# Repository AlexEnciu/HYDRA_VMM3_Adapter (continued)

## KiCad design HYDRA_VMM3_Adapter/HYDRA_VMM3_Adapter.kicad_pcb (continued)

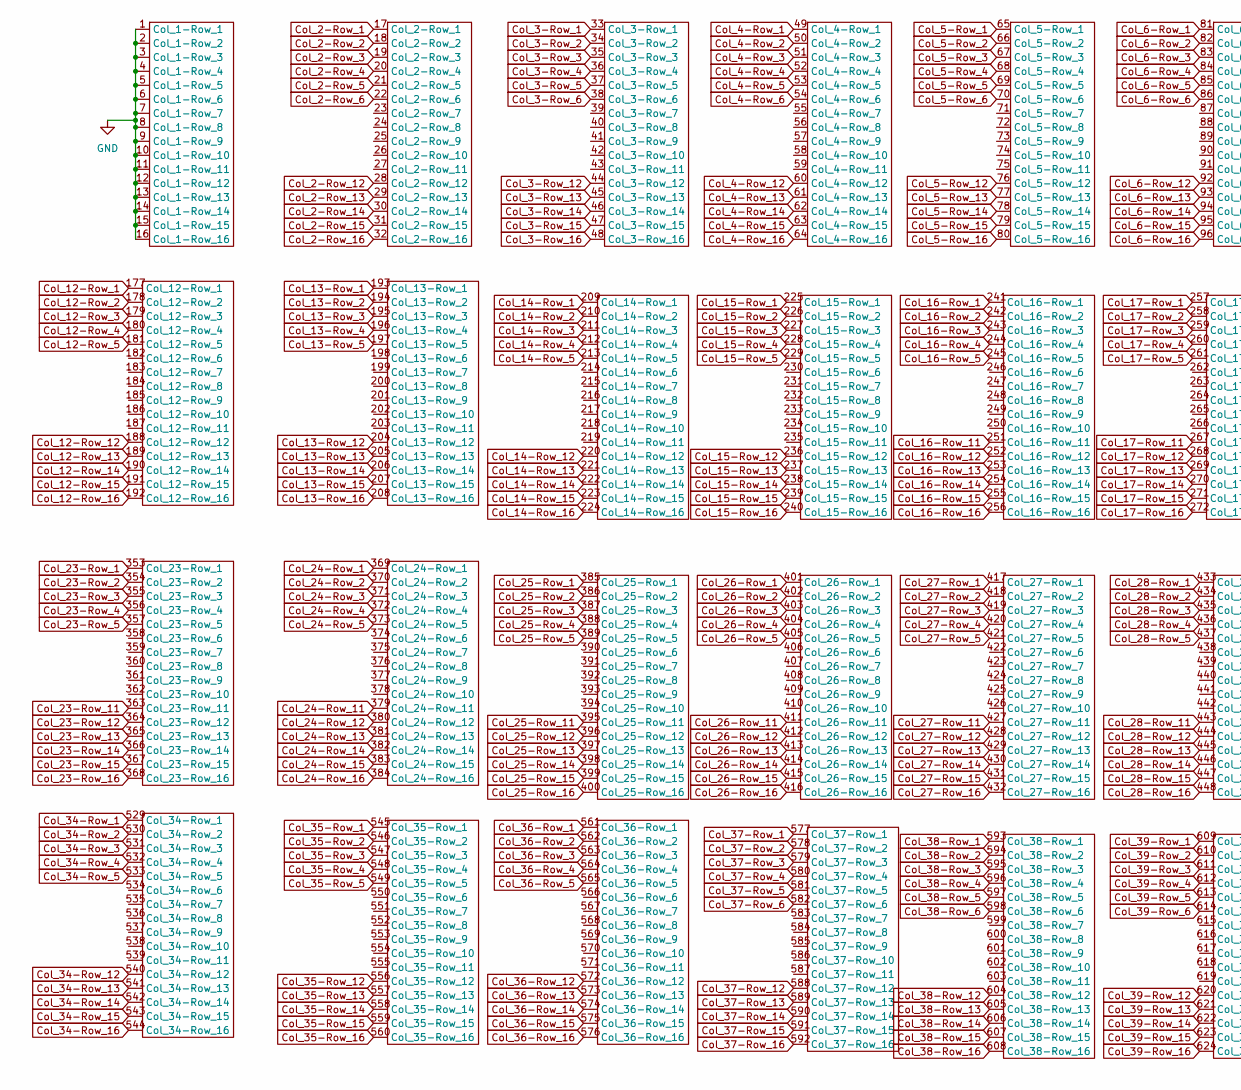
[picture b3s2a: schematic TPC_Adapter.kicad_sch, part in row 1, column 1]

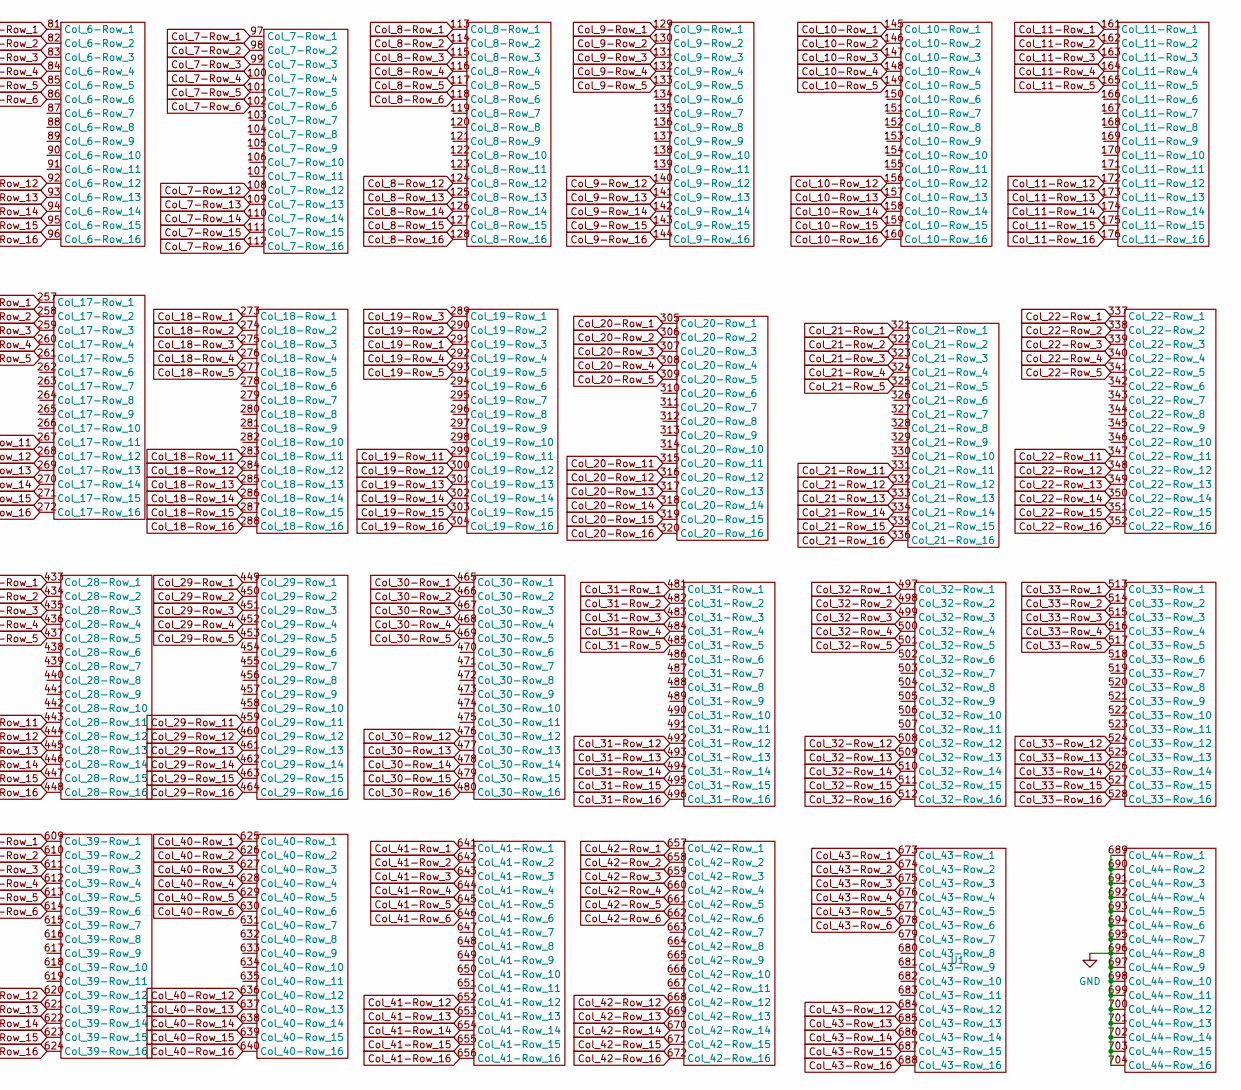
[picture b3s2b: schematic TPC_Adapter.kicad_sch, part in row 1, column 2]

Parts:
U1: TPC_Adapter_Footprint

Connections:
Col_2-Row_1: U1.17 (Col_2-Row_1); also elsewhere on the board
Col_2-Row_2: U1.18 (Col_2-Row_2); also elsewhere on the board
Col_2-Row_3: U1.19 (Col_2-Row_3); also elsewhere on the board
Col_2-Row_4: U1.20 (Col_2-Row_4); also elsewhere on the board
Col_2-Row_5: U1.21 (Col_2-Row_5); also elsewhere on the board
Col_2-Row_6: U1.22 (Col_2-Row_6); also elsewhere on the board
Col_2-Row_12: U1.28 (Col_2-Row_12); also elsewhere on the board
Col_2-Row_13: U1.29 (Col_2-Row_13); also elsewhere on the board
Col_2-Row_14: U1.30 (Col_2-Row_14); also elsewhere on the board
Col_2-Row_15: U1.31 (Col_2-Row_15); also elsewhere on the board
Col_2-Row_16: U1.32 (Col_2-Row_16); also elsewhere on the board
Col_3-Row_1: U1.33 (Col_3-Row_1); also elsewhere on the board
Col_3-Row_2: U1.34 (Col_3-Row_2); also elsewhere on the board
Col_3-Row_3: U1.35 (Col_3-Row_3); also elsewhere on the board
Col_3-Row_4: U1.36 (Col_3-Row_4); also elsewhere on the board
Col_3-Row_5: U1.37 (Col_3-Row_5); also elsewhere on the board
Col_3-Row_6: U1.38 (Col_3-Row_6); also elsewhere on the board
Col_3-Row_12: U1.44 (Col_3-Row_12); also elsewhere on the board
Col_3-Row_13: U1.45 (Col_3-Row_13); also elsewhere on the board
Col_3-Row_14: U1.46 (Col_3-Row_14); also elsewhere on the board
Col_3-Row_15: U1.47 (Col_3-Row_15); also elsewhere on the board
Col_3-Row_16: U1.48 (Col_3-Row_16); also elsewhere on the board
Col_4-Row_1: U1.49 (Col_4-Row_1); also elsewhere on the board
Col_4-Row_2: U1.50 (Col_4-Row_2); also elsewhere on the board
Col_4-Row_3: U1.51 (Col_4-Row_3); also elsewhere on the board
Col_4-Row_4: U1.52 (Col_4-Row_4); also elsewhere on the board
Col_4-Row_5: U1.53 (Col_4-Row_5); also elsewhere on the board
Col_4-Row_6: U1.54 (Col_4-Row_6); also elsewhere on the board
Col_4-Row_12: U1.60 (Col_4-Row_12); also elsewhere on the board
Col_4-Row_13: U1.61 (Col_4-Row_13); also elsewhere on the board
Col_4-Row_14: U1.62 (Col_4-Row_14); also elsewhere on the board
Col_4-Row_15: U1.63 (Col_4-Row_15); also elsewhere on the board
Col_4-Row_16: U1.64 (Col_4-Row_16); also elsewhere on the board
Col_5-Row_1: U1.65 (Col_5-Row_1); also elsewhere on the board
Col_5-Row_2: U1.66 (Col_5-Row_2); also elsewhere on the board
Col_5-Row_3: U1.67 (Col_5-Row_3); also elsewhere on the board
Col_5-Row_4: U1.68 (Col_5-Row_4); also elsewhere on the board
Col_5-Row_5: U1.69 (Col_5-Row_5); also elsewhere on the board
Col_5-Row_6: U1.70 (Col_5-Row_6); also elsewhere on the board
Col_5-Row_12: U1.76 (Col_5-Row_12); also elsewhere on the board
Col_5-Row_13: U1.77 (Col_5-Row_13); also elsewhere on the board
Col_5-Row_14: U1.78 (Col_5-Row_14); also elsewhere on the board
Col_5-Row_15: U1.79 (Col_5-Row_15); also elsewhere on the board
Col_5-Row_16: U1.80 (Col_5-Row_16); also elsewhere on the board
Col_6-Row_1: U1.81 (Col_6-Row_1); also elsewhere on the board
Col_6-Row_2: U1.82 (Col_6-Row_2); also elsewhere on the board
Col_6-Row_3: U1.83 (Col_6-Row_3); also elsewhere on the board
Col_6-Row_4: U1.84 (Col_6-Row_4); also elsewhere on the board
Col_6-Row_5: U1.85 (Col_6-Row_5); also elsewhere on the board
Col_6-Row_6: U1.86 (Col_6-Row_6); also elsewhere on the board
Col_6-Row_12: U1.92 (Col_6-Row_12); also elsewhere on the board
Col_6-Row_13: U1.93 (Col_6-Row_13); also elsewhere on the board
Col_6-Row_14: U1.94 (Col_6-Row_14); also elsewhere on the board
Col_6-Row_15: U1.95 (Col_6-Row_15); also elsewhere on the board
Col_6-Row_16: U1.96 (Col_6-Row_16); also elsewhere on the board
Col_7-Row_1: U1.97 (Col_7-Row_1); also elsewhere on the board
Col_7-Row_2: U1.98 (Col_7-Row_2); also elsewhere on the board
Col_7-Row_3: U1.99 (Col_7-Row_3); also elsewhere on the board
Col_7-Row_4: U1.100 (Col_7-Row_4); also elsewhere on the board
Col_7-Row_5: U1.101 (Col_7-Row_5); also elsewhere on the board
Col_7-Row_6: U1.102 (Col_7-Row_6); also elsewhere on the board
Col_7-Row_12: U1.108 (Col_7-Row_12); also elsewhere on the board
Col_7-Row_13: U1.109 (Col_7-Row_13); also elsewhere on the board
Col_7-Row_14: U1.110 (Col_7-Row_14); also elsewhere on the board
Col_7-Row_15: U1.111 (Col_7-Row_15); also elsewhere on the board
Col_7-Row_16: U1.112 (Col_7-Row_16); also elsewhere on the board
Col_8-Row_1: U1.113 (Col_8-Row_1); also elsewhere on the board
Col_8-Row_2: U1.114 (Col_8-Row_2); also elsewhere on the board
Col_8-Row_3: U1.115 (Col_8-Row_3); also elsewhere on the board
Col_8-Row_4: U1.116 (Col_8-Row_4); also elsewhere on the board
Col_8-Row_5: U1.117 (Col_8-Row_5); also elsewhere on the board
Col_8-Row_6: U1.118 (Col_8-Row_6); also elsewhere on the board
Col_8-Row_12: U1.124 (Col_8-Row_12); also elsewhere on the board
Col_8-Row_13: U1.125 (Col_8-Row_13); also elsewhere on the board
Col_8-Row_14: U1.126 (Col_8-Row_14); also elsewhere on the board
Col_8-Row_15: U1.127 (Col_8-Row_15); also elsewhere on the board
Col_8-Row_16: U1.128 (Col_8-Row_16); also elsewhere on the board
Col_9-Row_1: U1.129 (Col_9-Row_1); also elsewhere on the board
Col_9-Row_2: U1.130 (Col_9-Row_2); also elsewhere on the board
Col_9-Row_3: U1.131 (Col_9-Row_3); also elsewhere on the board
Col_9-Row_4: U1.132 (Col_9-Row_4); also elsewhere on the board
Col_9-Row_5: U1.133 (Col_9-Row_5); also elsewhere on the board
Col_9-Row_12: U1.140 (Col_9-Row_12); also elsewhere on the board
Col_9-Row_13: U1.141 (Col_9-Row_13); also elsewhere on the board
Col_9-Row_14: U1.142 (Col_9-Row_14); also elsewhere on the board
Col_9-Row_15: U1.143 (Col_9-Row_15); also elsewhere on the board
Col_9-Row_16: U1.144 (Col_9-Row_16); also elsewhere on the board
Col_10-Row_1: U1.145 (Col_10-Row_1); also elsewhere on the board
Col_10-Row_2: U1.146 (Col_10-Row_2); also elsewhere on the board
Col_10-Row_3: U1.147 (Col_10-Row_3); also elsewhere on the board
Col_10-Row_4: U1.148 (Col_10-Row_4); also elsewhere on the board
Col_10-Row_5: U1.149 (Col_10-Row_5); also elsewhere on the board
Col_10-Row_12: U1.156 (Col_10-Row_12); also elsewhere on the board
Col_10-Row_13: U1.157 (Col_10-Row_13); also elsewhere on the board
Col_10-Row_14: U1.158 (Col_10-Row_14); also elsewhere on the board
Col_10-Row_15: U1.159 (Col_10-Row_15); also elsewhere on the board
Col_10-Row_16: U1.160 (Col_10-Row_16); also elsewhere on the board
Col_11-Row_1: U1.161 (Col_11-Row_1); also elsewhere on the board
Col_11-Row_2: U1.162 (Col_11-Row_2); also elsewhere on the board
Col_11-Row_3: U1.163 (Col_11-Row_3); also elsewhere on the board
Col_11-Row_4: U1.164 (Col_11-Row_4); also elsewhere on the board
Col_11-Row_5: U1.165 (Col_11-Row_5); also elsewhere on the board
Col_11-Row_12: U1.172 (Col_11-Row_12); also elsewhere on the board
Col_11-Row_13: U1.173 (Col_11-Row_13); also elsewhere on the board
Col_11-Row_14: U1.174 (Col_11-Row_14); also elsewhere on the board
Col_11-Row_15: U1.175 (Col_11-Row_15); also elsewhere on the board
Col_11-Row_16: U1.176 (Col_11-Row_16); also elsewhere on the board
Col_12-Row_1: U1.177 (Col_12-Row_1); also elsewhere on the board
Col_12-Row_2: U1.178 (Col_12-Row_2); also elsewhere on the board
Col_12-Row_3: U1.179 (Col_12-Row_3); also elsewhere on the board
Col_12-Row_4: U1.180 (Col_12-Row_4); also elsewhere on the board
Col_12-Row_5: U1.181 (Col_12-Row_5); also elsewhere on the board
Col_12-Row_12: U1.188 (Col_12-Row_12); also elsewhere on the board
Col_12-Row_13: U1.189 (Col_12-Row_13); also elsewhere on the board
Col_12-Row_14: U1.190 (Col_12-Row_14); also elsewhere on the board
Col_12-Row_15: U1.191 (Col_12-Row_15); also elsewhere on the board
Col_12-Row_16: U1.192 (Col_12-Row_16); also elsewhere on the board
Col_13-Row_1: U1.193 (Col_13-Row_1); also elsewhere on the board
Col_13-Row_2: U1.194 (Col_13-Row_2); also elsewhere on the board
Col_13-Row_3: U1.195 (Col_13-Row_3); also elsewhere on the board
Col_13-Row_4: U1.196 (Col_13-Row_4); also elsewhere on the board
Col_13-Row_5: U1.197 (Col_13-Row_5); also elsewhere on the board
Col_13-Row_12: U1.204 (Col_13-Row_12); also elsewhere on the board
Col_13-Row_13: U1.205 (Col_13-Row_13); also elsewhere on the board
Col_13-Row_14: U1.206 (Col_13-Row_14); also elsewhere on the board
Col_13-Row_15: U1.207 (Col_13-Row_15); also elsewhere on the board
Col_13-Row_16: U1.208 (Col_13-Row_16); also elsewhere on the board
Col_14-Row_1: U1.209 (Col_14-Row_1); also elsewhere on the board
Col_14-Row_2: U1.210 (Col_14-Row_2); also elsewhere on the board
Col_14-Row_3: U1.211 (Col_14-Row_3); also elsewhere on the board
Col_14-Row_4: U1.212 (Col_14-Row_4); also elsewhere on the board
Col_14-Row_5: U1.213 (Col_14-Row_5); also elsewhere on the board
Col_14-Row_12: U1.220 (Col_14-Row_12); also elsewhere on the board
Col_14-Row_13: U1.221 (Col_14-Row_13); also elsewhere on the board
Col_14-Row_14: U1.222 (Col_14-Row_14); also elsewhere on the board
Col_14-Row_15: U1.223 (Col_14-Row_15); also elsewhere on the board
Col_14-Row_16: U1.224 (Col_14-Row_16); also elsewhere on the board
Col_15-Row_1: U1.225 (Col_15-Row_1); also elsewhere on the board
Col_15-Row_2: U1.226 (Col_15-Row_2); also elsewhere on the board
Col_15-Row_3: U1.227 (Col_15-Row_3); also elsewhere on the board
Col_15-Row_4: U1.228 (Col_15-Row_4); also elsewhere on the board
Col_15-Row_5: U1.229 (Col_15-Row_5); also elsewhere on the board
Col_15-Row_12: U1.236 (Col_15-Row_12); also elsewhere on the board
Col_15-Row_13: U1.237 (Col_15-Row_13); also elsewhere on the board
Col_15-Row_14: U1.238 (Col_15-Row_14); also elsewhere on the board
Col_15-Row_15: U1.239 (Col_15-Row_15); also elsewhere on the board
Col_15-Row_16: U1.240 (Col_15-Row_16); also elsewhere on the board
Col_16-Row_1: U1.241 (Col_16-Row_1); also elsewhere on the board
Col_16-Row_2: U1.242 (Col_16-Row_2); also elsewhere on the board
Col_16-Row_3: U1.243 (Col_16-Row_3); also elsewhere on the board
Col_16-Row_4: U1.244 (Col_16-Row_4); also elsewhere on the board
Col_16-Row_5: U1.245 (Col_16-Row_5); also elsewhere on the board
Col_16-Row_11: U1.251 (Col_16-Row_11); also elsewhere on the board
Col_16-Row_12: U1.252 (Col_16-Row_12); also elsewhere on the board
Col_16-Row_13: U1.253 (Col_16-Row_13); also elsewhere on the board
Col_16-Row_14: U1.254 (Col_16-Row_14); also elsewhere on the board
Col_16-Row_15: U1.255 (Col_16-Row_15); also elsewhere on the board
Col_16-Row_16: U1.256 (Col_16-Row_16); also elsewhere on the board
Col_17-Row_1: U1.257 (Col_17-Row_1); also elsewhere on the board
Col_17-Row_2: U1.258 (Col_17-Row_2); also elsewhere on the board
Col_17-Row_3: U1.259 (Col_17-Row_3); also elsewhere on the board
Col_17-Row_4: U1.260 (Col_17-Row_4); also elsewhere on the board
Col_17-Row_5: U1.261 (Col_17-Row_5); also elsewhere on the board
Col_17-Row_11: U1.267 (Col_17-Row_11); also elsewhere on the board
Col_17-Row_12: U1.268 (Col_17-Row_12); also elsewhere on the board
Col_17-Row_13: U1.269 (Col_17-Row_13); also elsewhere on the board
Col_17-Row_14: U1.270 (Col_17-Row_14); also elsewhere on the board
Col_17-Row_15: U1.271 (Col_17-Row_15); also elsewhere on the board
Col_17-Row_16: U1.272 (Col_17-Row_16); also elsewhere on the board
Col_18-Row_1: U1.273 (Col_18-Row_1); also elsewhere on the board
Col_18-Row_2: U1.274 (Col_18-Row_2); also elsewhere on the board
Col_18-Row_3: U1.275 (Col_18-Row_3); also elsewhere on the board
Col_18-Row_4: U1.276 (Col_18-Row_4); also elsewhere on the board
Col_18-Row_5: U1.277 (Col_18-Row_5); also elsewhere on the board
Col_18-Row_11: U1.283 (Col_18-Row_11); also elsewhere on the board
Col_18-Row_12: U1.284 (Col_18-Row_12); also elsewhere on the board
Col_18-Row_13: U1.285 (Col_18-Row_13); also elsewhere on the board
Col_18-Row_14: U1.286 (Col_18-Row_14); also elsewhere on the board
Col_18-Row_15: U1.287 (Col_18-Row_15); also elsewhere on the board
Col_18-Row_16: U1.288 (Col_18-Row_16); also elsewhere on the board
Col_19-Row_1: U1.291 (Col_19-Row_3); also elsewhere on the board
Col_19-Row_2: U1.290 (Col_19-Row_2); also elsewhere on the board
Col_19-Row_3: U1.289 (Col_19-Row_1); also elsewhere on the board
Col_19-Row_4: U1.292 (Col_19-Row_4); also elsewhere on the board
Col_19-Row_5: U1.293 (Col_19-Row_5); also elsewhere on the board
Col_19-Row_11: U1.299 (Col_19-Row_11); also elsewhere on the board
Col_19-Row_12: U1.300 (Col_19-Row_12); also elsewhere on the board
Col_19-Row_13: U1.301 (Col_19-Row_13); also elsewhere on the board
Col_19-Row_14: U1.302 (Col_19-Row_14); also elsewhere on the board
Col_19-Row_15: U1.303 (Col_19-Row_15); also elsewhere on the board
Col_19-Row_16: U1.304 (Col_19-Row_16); also elsewhere on the board
Col_20-Row_1: U1.305 (Col_20-Row_1); also elsewhere on the board
Col_20-Row_2: U1.306 (Col_20-Row_2); also elsewhere on the board
Col_20-Row_3: U1.307 (Col_20-Row_3); also elsewhere on the board
Col_20-Row_4: U1.308 (Col_20-Row_4); also elsewhere on the board
Col_20-Row_5: U1.309 (Col_20-Row_5); also elsewhere on the board
Col_20-Row_11: U1.315 (Col_20-Row_11); also elsewhere on the board
Col_20-Row_12: U1.316 (Col_20-Row_12); also elsewhere on the board
Col_20-Row_13: U1.317 (Col_20-Row_13); also elsewhere on the board
Col_20-Row_14: U1.318 (Col_20-Row_14); also elsewhere on the board
Col_20-Row_15: U1.319 (Col_20-Row_15); also elsewhere on the board
Col_20-Row_16: U1.320 (Col_20-Row_16); also elsewhere on the board
Col_21-Row_1: U1.321 (Col_21-Row_1); also elsewhere on the board
Col_21-Row_2: U1.322 (Col_21-Row_2); also elsewhere on the board
Col_21-Row_3: U1.323 (Col_21-Row_3); also elsewhere on the board
Col_21-Row_4: U1.324 (Col_21-Row_4); also elsewhere on the board
Col_21-Row_5: U1.325 (Col_21-Row_5); also elsewhere on the board
Col_21-Row_11: U1.331 (Col_21-Row_11); also elsewhere on the board
Col_21-Row_12: U1.332 (Col_21-Row_12); also elsewhere on the board
Col_21-Row_13: U1.333 (Col_21-Row_13); also elsewhere on the board
Col_21-Row_14: U1.334 (Col_21-Row_14); also elsewhere on the board
Col_21-Row_15: U1.335 (Col_21-Row_15); also elsewhere on the board
Col_21-Row_16: U1.336 (Col_21-Row_16); also elsewhere on the board
Col_22-Row_1: U1.337 (Col_22-Row_1); also elsewhere on the board
Col_22-Row_2: U1.338 (Col_22-Row_2); also elsewhere on the board
Col_22-Row_3: U1.339 (Col_22-Row_3); also elsewhere on the board
Col_22-Row_4: U1.340 (Col_22-Row_4); also elsewhere on the board
Col_22-Row_5: U1.341 (Col_22-Row_5); also elsewhere on the board
Col_22-Row_11: U1.347 (Col_22-Row_11); also elsewhere on the board
Col_22-Row_12: U1.348 (Col_22-Row_12); also elsewhere on the board
Col_22-Row_13: U1.349 (Col_22-Row_13); also elsewhere on the board
Col_22-Row_14: U1.350 (Col_22-Row_14); also elsewhere on the board
Col_22-Row_15: U1.351 (Col_22-Row_15); also elsewhere on the board
Col_22-Row_16: U1.352 (Col_22-Row_16); also elsewhere on the board
Col_23-Row_1: U1.353 (Col_23-Row_1); also elsewhere on the board
Col_23-Row_2: U1.354 (Col_23-Row_2); also elsewhere on the board
Col_23-Row_3: U1.355 (Col_23-Row_3); also elsewhere on the board
Col_23-Row_4: U1.356 (Col_23-Row_4); also elsewhere on the board
Col_23-Row_5: U1.357 (Col_23-Row_5); also elsewhere on the board
Col_23-Row_11: U1.363 (Col_23-Row_11); also elsewhere on the board
Col_23-Row_12: U1.364 (Col_23-Row_12); also elsewhere on the board
Col_23-Row_13: U1.365 (Col_23-Row_13); also elsewhere on the board
Col_23-Row_14: U1.366 (Col_23-Row_14); also elsewhere on the board
Col_23-Row_15: U1.367 (Col_23-Row_15); also elsewhere on the board
Col_23-Row_16: U1.368 (Col_23-Row_16); also elsewhere on the board
Col_24-Row_1: U1.369 (Col_24-Row_1); also elsewhere on the board
Col_24-Row_2: U1.370 (Col_24-Row_2); also elsewhere on the board
Col_24-Row_3: U1.371 (Col_24-Row_3); also elsewhere on the board
Col_24-Row_4: U1.372 (Col_24-Row_4); also elsewhere on the board
Col_24-Row_5: U1.373 (Col_24-Row_5); also elsewhere on the board
Col_24-Row_11: U1.379 (Col_24-Row_11); also elsewhere on the board
Col_24-Row_12: U1.380 (Col_24-Row_12); also elsewhere on the board
Col_24-Row_13: U1.381 (Col_24-Row_13); also elsewhere on the board
Col_24-Row_14: U1.382 (Col_24-Row_14); also elsewhere on the board
Col_24-Row_15: U1.383 (Col_24-Row_15); also elsewhere on the board
Col_24-Row_16: U1.384 (Col_24-Row_16); also elsewhere on the board
Col_25-Row_1: U1.385 (Col_25-Row_1); also elsewhere on the board
Col_25-Row_2: U1.386 (Col_25-Row_2); also elsewhere on the board
Col_25-Row_3: U1.387 (Col_25-Row_3); also elsewhere on the board
Col_25-Row_4: U1.388 (Col_25-Row_4); also elsewhere on the board
Col_25-Row_5: U1.389 (Col_25-Row_5); also elsewhere on the board
Col_25-Row_11: U1.395 (Col_25-Row_11); also elsewhere on the board
Col_25-Row_12: U1.396 (Col_25-Row_12); also elsewhere on the board
Col_25-Row_13: U1.397 (Col_25-Row_13); also elsewhere on the board
Col_25-Row_14: U1.398 (Col_25-Row_14); also elsewhere on the board
Col_25-Row_15: U1.399 (Col_25-Row_15); also elsewhere on the board
Col_25-Row_16: U1.400 (Col_25-Row_16); also elsewhere on the board
Col_26-Row_1: U1.401 (Col_26-Row_1); also elsewhere on the board
Col_26-Row_2: U1.402 (Col_26-Row_2); also elsewhere on the board
Col_26-Row_3: U1.403 (Col_26-Row_3); also elsewhere on the board
Col_26-Row_4: U1.404 (Col_26-Row_4); also elsewhere on the board
Col_26-Row_5: U1.405 (Col_26-Row_5); also elsewhere on the board
Col_26-Row_11: U1.411 (Col_26-Row_11); also elsewhere on the board
Col_26-Row_12: U1.412 (Col_26-Row_12); also elsewhere on the board
Col_26-Row_13: U1.413 (Col_26-Row_13); also elsewhere on the board
Col_26-Row_14: U1.414 (Col_26-Row_14); also elsewhere on the board
Col_26-Row_15: U1.415 (Col_26-Row_15); also elsewhere on the board
Col_26-Row_16: U1.416 (Col_26-Row_16); also elsewhere on the board
Col_27-Row_1: U1.417 (Col_27-Row_1); also elsewhere on the board
Col_27-Row_2: U1.418 (Col_27-Row_2); also elsewhere on the board
Col_27-Row_3: U1.419 (Col_27-Row_3); also elsewhere on the board
Col_27-Row_4: U1.420 (Col_27-Row_4); also elsewhere on the board
Col_27-Row_5: U1.421 (Col_27-Row_5); also elsewhere on the board
Col_27-Row_11: U1.427 (Col_27-Row_11); also elsewhere on the board
Col_27-Row_12: U1.428 (Col_27-Row_12); also elsewhere on the board
Col_27-Row_13: U1.429 (Col_27-Row_13); also elsewhere on the board
Col_27-Row_14: U1.430 (Col_27-Row_14); also elsewhere on the board
Col_27-Row_15: U1.431 (Col_27-Row_15); also elsewhere on the board
Col_27-Row_16: U1.432 (Col_27-Row_16); also elsewhere on the board
Col_28-Row_1: U1.433 (Col_28-Row_1); also elsewhere on the board
Col_28-Row_2: U1.434 (Col_28-Row_2); also elsewhere on the board
Col_28-Row_3: U1.435 (Col_28-Row_3); also elsewhere on the board
Col_28-Row_4: U1.436 (Col_28-Row_4); also elsewhere on the board
Col_28-Row_5: U1.437 (Col_28-Row_5); also elsewhere on the board
Col_28-Row_11: U1.443 (Col_28-Row_11); also elsewhere on the board
Col_28-Row_12: U1.444 (Col_28-Row_12); also elsewhere on the board
Col_28-Row_13: U1.445 (Col_28-Row_13); also elsewhere on the board
Col_28-Row_14: U1.446 (Col_28-Row_14); also elsewhere on the board
Col_28-Row_15: U1.447 (Col_28-Row_15); also elsewhere on the board
Col_28-Row_16: U1.448 (Col_28-Row_16); also elsewhere on the board
Col_29-Row_1: U1.449 (Col_29-Row_1); also elsewhere on the board
Col_29-Row_2: U1.450 (Col_29-Row_2); also elsewhere on the board
Col_29-Row_3: U1.451 (Col_29-Row_3); also elsewhere on the board
Col_29-Row_4: U1.452 (Col_29-Row_4); also elsewhere on the board
Col_29-Row_5: U1.453 (Col_29-Row_5); also elsewhere on the board
Col_29-Row_11: U1.459 (Col_29-Row_11); also elsewhere on the board
Col_29-Row_12: U1.460 (Col_29-Row_12); also elsewhere on the board
Col_29-Row_13: U1.461 (Col_29-Row_13); also elsewhere on the board
Col_29-Row_14: U1.462 (Col_29-Row_14); also elsewhere on the board
Col_29-Row_15: U1.463 (Col_29-Row_15); also elsewhere on the board
Col_29-Row_16: U1.464 (Col_29-Row_16); also elsewhere on the board
Col_30-Row_1: U1.465 (Col_30-Row_1); also elsewhere on the board
Col_30-Row_2: U1.466 (Col_30-Row_2); also elsewhere on the board
Col_30-Row_3: U1.467 (Col_30-Row_3); also elsewhere on the board
Col_30-Row_4: U1.468 (Col_30-Row_4); also elsewhere on the board
Col_30-Row_5: U1.469 (Col_30-Row_5); also elsewhere on the board
Col_30-Row_12: U1.476 (Col_30-Row_12); also elsewhere on the board
Col_30-Row_13: U1.477 (Col_30-Row_13); also elsewhere on the board
Col_30-Row_14: U1.478 (Col_30-Row_14); also elsewhere on the board
Col_30-Row_15: U1.479 (Col_30-Row_15); also elsewhere on the board
Col_30-Row_16: U1.480 (Col_30-Row_16); also elsewhere on the board
Col_31-Row_1: U1.481 (Col_31-Row_1); also elsewhere on the board
Col_31-Row_2: U1.482 (Col_31-Row_2); also elsewhere on the board
Col_31-Row_3: U1.483 (Col_31-Row_3); also elsewhere on the board
Col_31-Row_4: U1.484 (Col_31-Row_4); also elsewhere on the board
Col_31-Row_5: U1.485 (Col_31-Row_5); also elsewhere on the board
Col_31-Row_12: U1.492 (Col_31-Row_12); also elsewhere on the board
Col_31-Row_13: U1.493 (Col_31-Row_13); also elsewhere on the board
Col_31-Row_14: U1.494 (Col_31-Row_14); also elsewhere on the board
Col_31-Row_15: U1.495 (Col_31-Row_15); also elsewhere on the board
Col_31-Row_16: U1.496 (Col_31-Row_16); also elsewhere on the board
Col_32-Row_1: U1.497 (Col_32-Row_1); also elsewhere on the board
Col_32-Row_2: U1.498 (Col_32-Row_2); also elsewhere on the board
Col_32-Row_3: U1.499 (Col_32-Row_3); also elsewhere on the board
Col_32-Row_4: U1.500 (Col_32-Row_4); also elsewhere on the board
Col_32-Row_5: U1.501 (Col_32-Row_5); also elsewhere on the board
Col_32-Row_12: U1.508 (Col_32-Row_12); also elsewhere on the board
Col_32-Row_13: U1.509 (Col_32-Row_13); also elsewhere on the board
Col_32-Row_14: U1.510 (Col_32-Row_14); also elsewhere on the board
Col_32-Row_15: U1.511 (Col_32-Row_15); also elsewhere on the board
Col_32-Row_16: U1.512 (Col_32-Row_16); also elsewhere on the board
Col_33-Row_1: U1.513 (Col_33-Row_1); also elsewhere on the board
Col_33-Row_2: U1.514 (Col_33-Row_2); also elsewhere on the board
Col_33-Row_3: U1.515 (Col_33-Row_3); also elsewhere on the board
Col_33-Row_4: U1.516 (Col_33-Row_4); also elsewhere on the board
Col_33-Row_5: U1.517 (Col_33-Row_5); also elsewhere on the board
Col_33-Row_12: U1.524 (Col_33-Row_12); also elsewhere on the board
Col_33-Row_13: U1.525 (Col_33-Row_13); also elsewhere on the board
Col_33-Row_14: U1.526 (Col_33-Row_14); also elsewhere on the board
Col_33-Row_15: U1.527 (Col_33-Row_15); also elsewhere on the board
Col_33-Row_16: U1.528 (Col_33-Row_16); also elsewhere on the board
Col_34-Row_1: U1.529 (Col_34-Row_1); also elsewhere on the board
Col_34-Row_2: U1.530 (Col_34-Row_2); also elsewhere on the board
Col_34-Row_3: U1.531 (Col_34-Row_3); also elsewhere on the board
Col_34-Row_4: U1.532 (Col_34-Row_4); also elsewhere on the board
Col_34-Row_5: U1.533 (Col_34-Row_5); also elsewhere on the board
Col_34-Row_12: U1.540 (Col_34-Row_12); also elsewhere on the board
Col_34-Row_13: U1.541 (Col_34-Row_13); also elsewhere on the board
Col_34-Row_14: U1.542 (Col_34-Row_14); also elsewhere on the board
Col_34-Row_15: U1.543 (Col_34-Row_15); also elsewhere on the board
Col_34-Row_16: U1.544 (Col_34-Row_16); also elsewhere on the board
Col_35-Row_1: U1.545 (Col_35-Row_1); also elsewhere on the board
Col_35-Row_2: U1.546 (Col_35-Row_2); also elsewhere on the board
Col_35-Row_3: U1.547 (Col_35-Row_3); also elsewhere on the board
Col_35-Row_4: U1.548 (Col_35-Row_4); also elsewhere on the board
Col_35-Row_5: U1.549 (Col_35-Row_5); also elsewhere on the board
Col_35-Row_12: U1.556 (Col_35-Row_12); also elsewhere on the board
Col_35-Row_13: U1.557 (Col_35-Row_13); also elsewhere on the board
Col_35-Row_14: U1.558 (Col_35-Row_14); also elsewhere on the board
Col_35-Row_15: U1.559 (Col_35-Row_15); also elsewhere on the board
Col_35-Row_16: U1.560 (Col_35-Row_16); also elsewhere on the board
Col_36-Row_1: U1.561 (Col_36-Row_1); also elsewhere on the board
Col_36-Row_2: U1.562 (Col_36-Row_2); also elsewhere on the board
Col_36-Row_3: U1.563 (Col_36-Row_3); also elsewhere on the board
Col_36-Row_4: U1.564 (Col_36-Row_4); also elsewhere on the board
Col_36-Row_5: U1.565 (Col_36-Row_5); also elsewhere on the board
Col_36-Row_12: U1.572 (Col_36-Row_12); also elsewhere on the board
Col_36-Row_13: U1.573 (Col_36-Row_13); also elsewhere on the board
Col_36-Row_14: U1.574 (Col_36-Row_14); also elsewhere on the board
Col_36-Row_15: U1.575 (Col_36-Row_15); also elsewhere on the board
Col_36-Row_16: U1.576 (Col_36-Row_16); also elsewhere on the board
Col_37-Row_1: U1.577 (Col_37-Row_1); also elsewhere on the board
Col_37-Row_2: U1.578 (Col_37-Row_2); also elsewhere on the board
Col_37-Row_3: U1.579 (Col_37-Row_3); also elsewhere on the board
Col_37-Row_4: U1.580 (Col_37-Row_4); also elsewhere on the board
Col_37-Row_5: U1.581 (Col_37-Row_5); also elsewhere on the board
Col_37-Row_6: U1.582 (Col_37-Row_6); also elsewhere on the board
Col_37-Row_12: U1.588 (Col_37-Row_12); also elsewhere on the board
Col_37-Row_13: U1.589 (Col_37-Row_13); also elsewhere on the board
Col_37-Row_14: U1.590 (Col_37-Row_14); also elsewhere on the board
Col_37-Row_15: U1.591 (Col_37-Row_15); also elsewhere on the board
Col_37-Row_16: U1.592 (Col_37-Row_16); also elsewhere on the board
Col_38-Row_1: U1.593 (Col_38-Row_1); also elsewhere on the board
Col_38-Row_2: U1.594 (Col_38-Row_2); also elsewhere on the board
Col_38-Row_3: U1.595 (Col_38-Row_3); also elsewhere on the board
Col_38-Row_4: U1.596 (Col_38-Row_4); also elsewhere on the board
Col_38-Row_5: U1.597 (Col_38-Row_5); also elsewhere on the board
Col_38-Row_6: U1.598 (Col_38-Row_6); also elsewhere on the board
Col_38-Row_12: U1.604 (Col_38-Row_12); also elsewhere on the board
Col_38-Row_13: U1.605 (Col_38-Row_13); also elsewhere on the board
Col_38-Row_14: U1.606 (Col_38-Row_14); also elsewhere on the board
Col_38-Row_15: U1.607 (Col_38-Row_15); also elsewhere on the board
Col_38-Row_16: U1.608 (Col_38-Row_16); also elsewhere on the board
Col_39-Row_1: U1.609 (Col_39-Row_1); also elsewhere on the board
Col_39-Row_2: U1.610 (Col_39-Row_2); also elsewhere on the board
Col_39-Row_3: U1.611 (Col_39-Row_3); also elsewhere on the board
Col_39-Row_4: U1.612 (Col_39-Row_4); also elsewhere on the board
Col_39-Row_5: U1.613 (Col_39-Row_5); also elsewhere on the board
Col_39-Row_6: U1.614 (Col_39-Row_6); also elsewhere on the board
Col_39-Row_12: U1.620 (Col_39-Row_12); also elsewhere on the board
Col_39-Row_13: U1.621 (Col_39-Row_13); also elsewhere on the board
Col_39-Row_14: U1.622 (Col_39-Row_14); also elsewhere on the board
Col_39-Row_15: U1.623 (Col_39-Row_15); also elsewhere on the board
Col_39-Row_16: U1.624 (Col_39-Row_16); also elsewhere on the board
Col_40-Row_1: U1.625 (Col_40-Row_1); also elsewhere on the board
Col_40-Row_2: U1.626 (Col_40-Row_2); also elsewhere on the board
Col_40-Row_3: U1.627 (Col_40-Row_3); also elsewhere on the board
Col_40-Row_4: U1.628 (Col_40-Row_4); also elsewhere on the board
Col_40-Row_5: U1.629 (Col_40-Row_5); also elsewhere on the board
Col_40-Row_6: U1.630 (Col_40-Row_6); also elsewhere on the board
Col_40-Row_12: U1.636 (Col_40-Row_12); also elsewhere on the board
Col_40-Row_13: U1.637 (Col_40-Row_13); also elsewhere on the board
Col_40-Row_14: U1.638 (Col_40-Row_14); also elsewhere on the board
Col_40-Row_15: U1.639 (Col_40-Row_15); also elsewhere on the board
Col_40-Row_16: U1.640 (Col_40-Row_16); also elsewhere on the board
Col_41-Row_1: U1.641 (Col_41-Row_1); also elsewhere on the board
Col_41-Row_2: U1.642 (Col_41-Row_2); also elsewhere on the board
Col_41-Row_3: U1.643 (Col_41-Row_3); also elsewhere on the board
Col_41-Row_4: U1.644 (Col_41-Row_4); also elsewhere on the board
Col_41-Row_5: U1.645 (Col_41-Row_5); also elsewhere on the board
Col_41-Row_6: U1.646 (Col_41-Row_6); also elsewhere on the board
Col_41-Row_12: U1.652 (Col_41-Row_12); also elsewhere on the board
Col_41-Row_13: U1.653 (Col_41-Row_13); also elsewhere on the board
Col_41-Row_14: U1.654 (Col_41-Row_14); also elsewhere on the board
Col_41-Row_15: U1.655 (Col_41-Row_15); also elsewhere on the board
Col_41-Row_16: U1.656 (Col_41-Row_16); also elsewhere on the board
Col_42-Row_1: U1.657 (Col_42-Row_1); also elsewhere on the board
Col_42-Row_2: U1.658 (Col_42-Row_2); also elsewhere on the board
Col_42-Row_3: U1.659 (Col_42-Row_3); also elsewhere on the board
Col_42-Row_4: U1.660 (Col_42-Row_4); also elsewhere on the board
Col_42-Row_5: U1.661 (Col_42-Row_5); also elsewhere on the board
Col_42-Row_6: U1.662 (Col_42-Row_6); also elsewhere on the board
Col_42-Row_12: U1.668 (Col_42-Row_12); also elsewhere on the board
Col_42-Row_13: U1.669 (Col_42-Row_13); also elsewhere on the board
Col_42-Row_14: U1.670 (Col_42-Row_14); also elsewhere on the board
Col_42-Row_15: U1.671 (Col_42-Row_15); also elsewhere on the board
Col_42-Row_16: U1.672 (Col_42-Row_16); also elsewhere on the board
Col_43-Row_1: U1.673 (Col_43-Row_1); also elsewhere on the board
Col_43-Row_2: U1.674 (Col_43-Row_2); also elsewhere on the board
Col_43-Row_3: U1.675 (Col_43-Row_3); also elsewhere on the board
Col_43-Row_4: U1.676 (Col_43-Row_4); also elsewhere on the board
Col_43-Row_5: U1.677 (Col_43-Row_5); also elsewhere on the board
Col_43-Row_6: U1.678 (Col_43-Row_6); also elsewhere on the board
Col_43-Row_12: U1.684 (Col_43-Row_12); also elsewhere on the board
Col_43-Row_13: U1.685 (Col_43-Row_13); also elsewhere on the board
Col_43-Row_14: U1.686 (Col_43-Row_14); also elsewhere on the board
Col_43-Row_15: U1.687 (Col_43-Row_15); also elsewhere on the board
Col_43-Row_16: U1.688 (Col_43-Row_16); also elsewhere on the board
GND: U1.1 (Col_1-Row_1), U1.2 (Col_1-Row_2), U1.3 (Col_1-Row_3), U1.4 (Col_1-Row_4), U1.5 (Col_1-Row_5), U1.6 (Col_1-Row_6), U1.7 (Col_1-Row_7), U1.8 (Col_1-Row_8), U1.9 (Col_1-Row_9), U1.10 (Col_1-Row_10), U1.11 (Col_1-Row_11), U1.12 (Col_1-Row_12), U1.13 (Col_1-Row_13), U1.14 (Col_1-Row_14), U1.15 (Col_1-Row_15), U1.16 (Col_1-Row_16), U1.689 (Col_44-Row_1), U1.690 (Col_44-Row_2), U1.691 (Col_44-Row_3), U1.692 (Col_44-Row_4), U1.693 (Col_44-Row_5), U1.694 (Col_44-Row_6), U1.695 (Col_44-Row_7), U1.696 (Col_44-Row_8), U1.697 (Col_44-Row_9), U1.698 (Col_44-Row_10), U1.699 (Col_44-Row_11), U1.700 (Col_44-Row_12), U1.701 (Col_44-Row_13), U1.702 (Col_44-Row_14), U1.703 (Col_44-Row_15), U1.704 (Col_44-Row_16); also elsewhere on the board

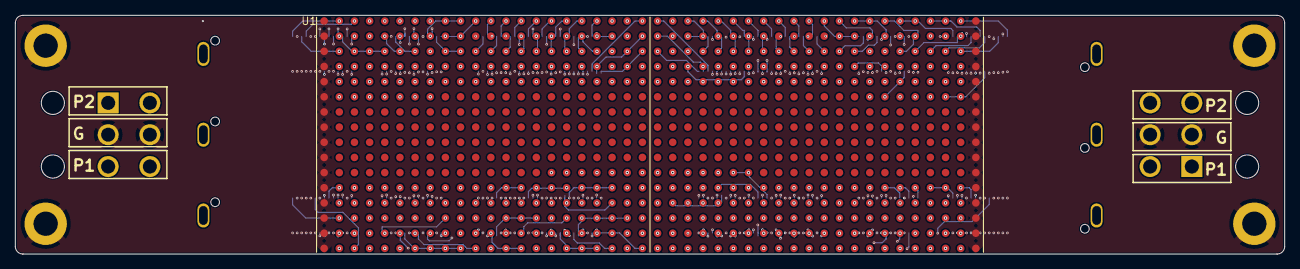
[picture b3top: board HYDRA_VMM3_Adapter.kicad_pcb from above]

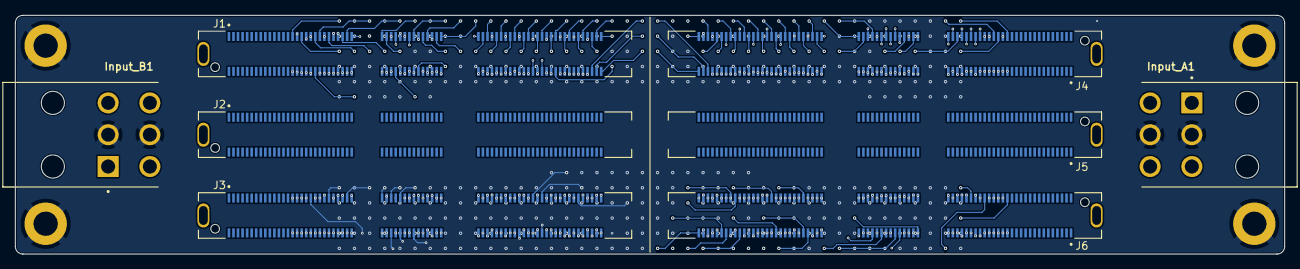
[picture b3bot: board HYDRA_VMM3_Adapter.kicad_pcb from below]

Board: 8 copper layers, 167.5 x 31.5 mm, 13 parts (8 on the bottom side), 453 nets.
